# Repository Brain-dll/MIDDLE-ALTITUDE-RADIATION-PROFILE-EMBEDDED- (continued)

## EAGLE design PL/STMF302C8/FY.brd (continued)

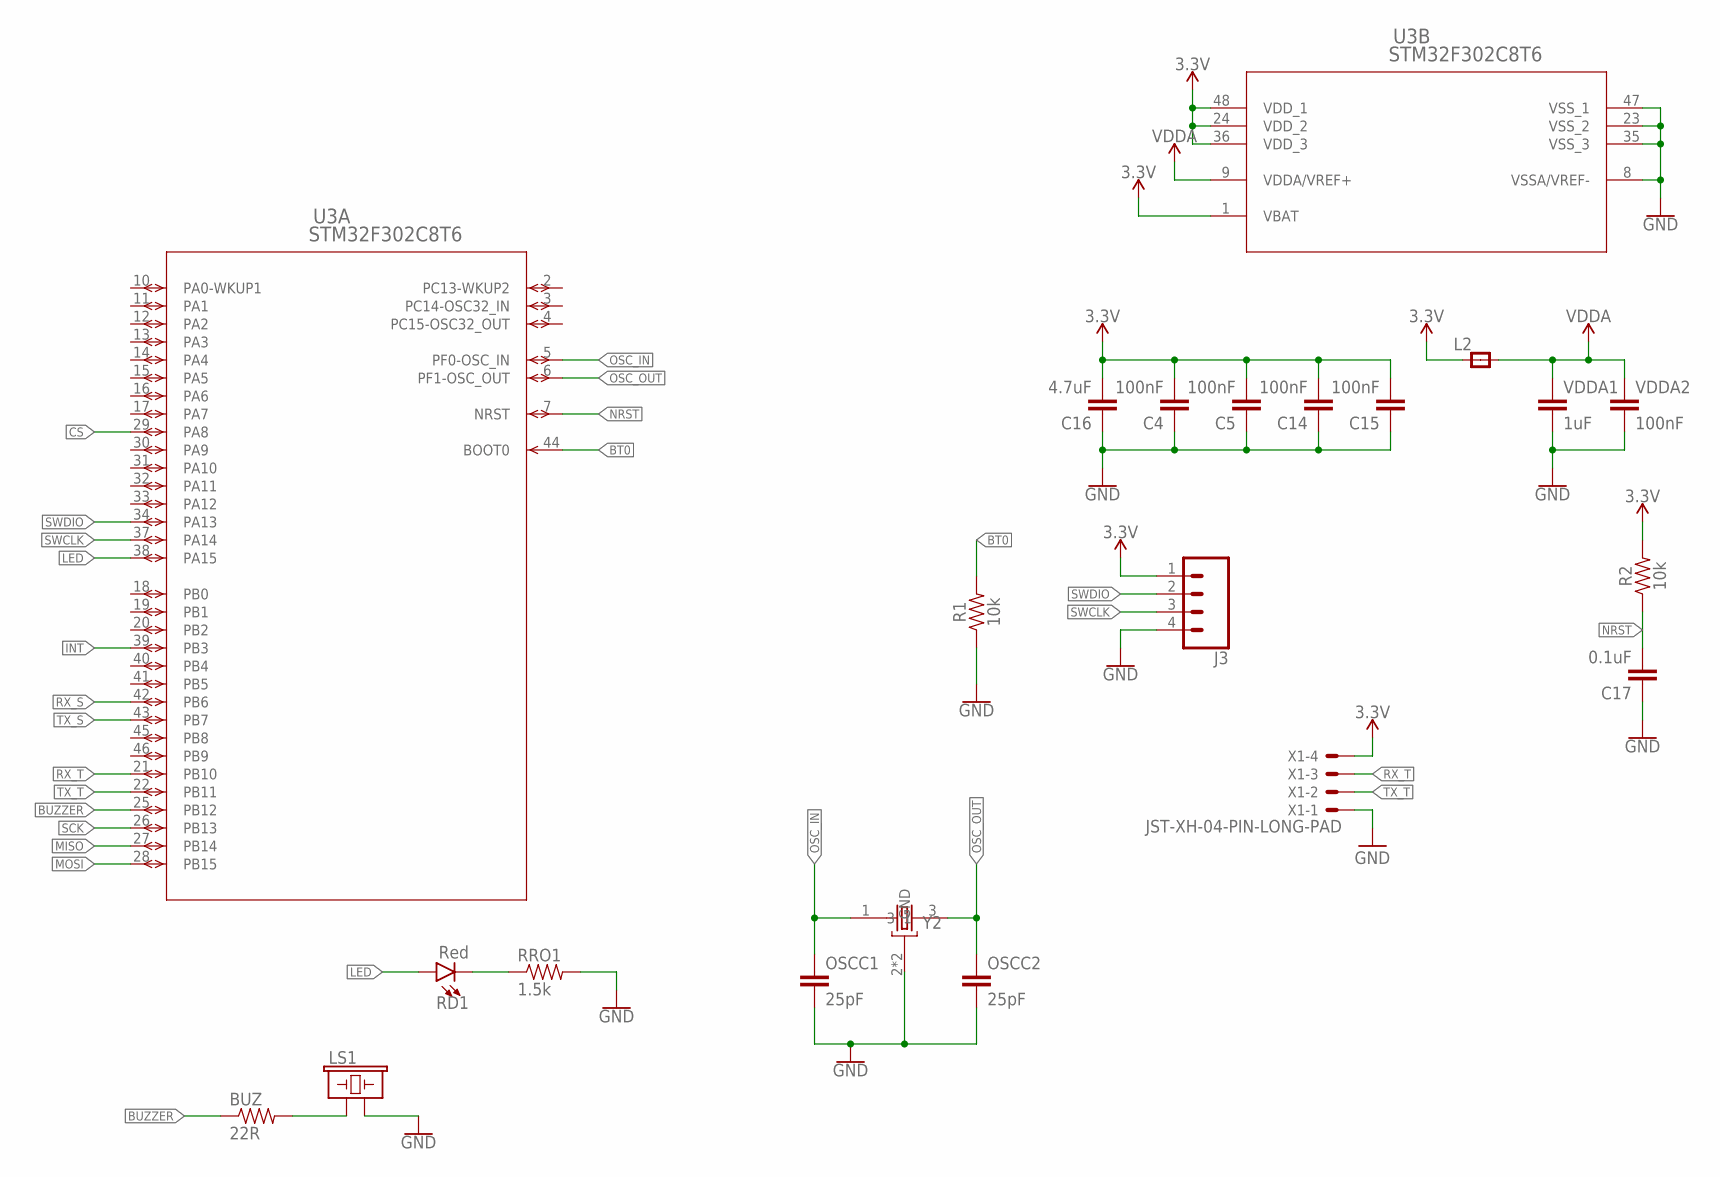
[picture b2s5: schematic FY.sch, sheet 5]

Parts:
BUZ: 22R; 0603-RES
C4, C5, C14, C15: 100nF; 0603
C16: 4.7uF; 0603
C17: 0.1uF; 0603
J3: CONN_04; 1X04
L2: RC-MASTER-SMD_FB_0805MP; RC-MASTER-SMD_L0805MP
LS1: BUZZER-PTH; BUZZER-12MM
OSCC1, OSCC2: 25pF; 0603
R1, R2: 10k; 0603
RD1: Red; LED-0603
RRO1: 1.5k; 0603-RES
U3: STM32F302C8T6; LQFP48-7X7MM
VDDA1: 1uF; 0603
VDDA2: 100nF; 0603
X1: JST-XH-04-PIN-LONG-PAD; JST-XH-04-PACKAGE-LONG-PAD
Y2: ABM2B-8.000MHZ-10-1-U-T; OSCCC500X320X110-4N

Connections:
3.3V: C4.2, C5.2, C14.2, C15.2, C16.2, J3.1, L2.1, R2.2, U3.1 (VBAT), U3.24 (VDD_2), U3.36 (VDD_3), U3.48 (VDD_1), X1.4; also elsewhere on the board
BT0: R1.2, U3.44 (BOOT0)
BUZZER: BUZ.1, U3.25 (PB12)
CS: U3.29 (PA8); also elsewhere on the board
GND: C4.1, C5.1, C14.1, C15.1, C16.1, C17.1, J3.4, LS1.- (2), OSCC1.2, OSCC2.2, R1.1, RRO1.2, U3.8 (VSSA/VREF-), U3.23 (VSS_2), U3.35 (VSS_3), U3.47 (VSS_1), VDDA1.2, VDDA2.2, X1.1, Y2.2 (GND), Y2.4 (GND); also elsewhere on the board
INT: U3.39 (PB3); also elsewhere on the board
LED: RD1.A, U3.38 (PA15)
MISO: U3.27 (PB14); also elsewhere on the board
MOSI: U3.28 (PB15); also elsewhere on the board
unnamed: RD1.C, RRO1.1
unnamed: BUZ.2, LS1.+ (1)
NRST: C17.2, R2.1, U3.7 (NRST)
OSC_IN: OSCC1.1, U3.5 (PF0-OSC_IN), Y2.1
OSC_OUT: OSCC2.1, U3.6 (PF1-OSC_OUT), Y2.3
RX_S: U3.42 (PB6); also elsewhere on the board
RX_T: U3.21 (PB10), X1.3
SCK: U3.26 (PB13); also elsewhere on the board
SWCLK: J3.3, U3.37 (PA14)
SWDIO: J3.2, U3.34 (PA13)
TX_S: U3.43 (PB7); also elsewhere on the board
TX_T: U3.22 (PB11), X1.2
VDDA: L2.2, U3.9 (VDDA/VREF+), VDDA1.1, VDDA2.1

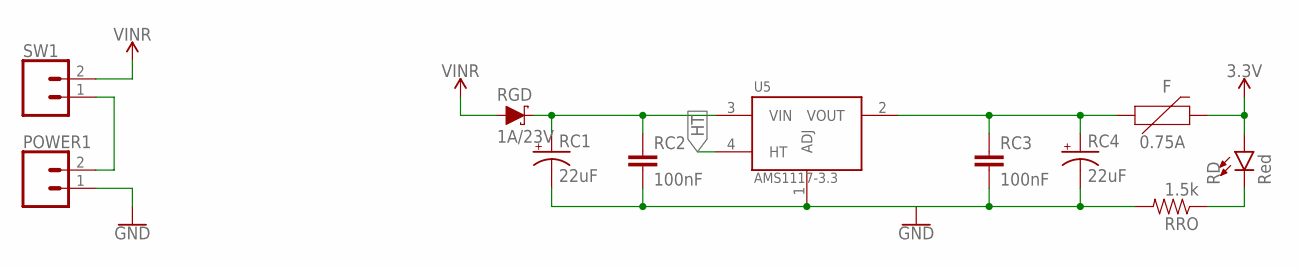
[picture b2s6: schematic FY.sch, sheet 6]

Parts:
F: 0.75A; 1206
POWER1: CONN_023.5MM-NO_SILK; SCREWTERMINAL-3.5MM-2-NS
RC1, RC4: 22uF; EIA3528
RC2, RC3: 100nF; 0603
RD: Red; LED-0603
RGD: 1A/23V; SOD-323
RRO: 1.5k; 0603-RES
SW1: CONN_023.5MM-NO_SILK; SCREWTERMINAL-3.5MM-2-NS
U5: AMS1117-3.3; SOT229P700X180-4N

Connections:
3.3V: F.2, RD.A; also elsewhere on the board
GND: POWER1.1, RC1.C (-), RC2.2, RC3.2, RC4.C (-), RRO.2, U5.1 (ADJ); also elsewhere on the board
HT: U5.4 (HT)
unnamed: POWER1.2, SW1.1
unnamed: F.1, RC3.1, RC4.A (+), U5.2 (VOUT)
unnamed: RD.C, RRO.1
VIN: RGD.A, SW1.2
VNR: RC1.A (+), RC2.1, RGD.C, U5.3 (VIN)

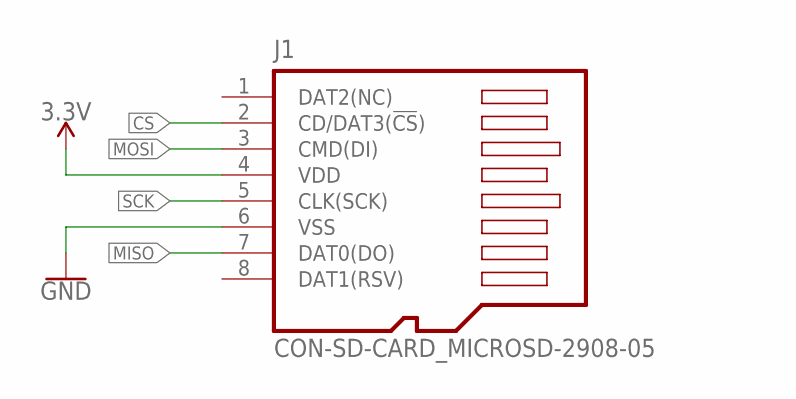
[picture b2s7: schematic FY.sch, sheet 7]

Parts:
J1: CON-SD-CARD_MICROSD-2908-05; CON-SD-CARD_2908-05

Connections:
3.3V: J1.4 (VDD); also elsewhere on the board
CS: J1.2 (CD/DAT3(!CS!)); also elsewhere on the board
GND: J1.6 (VSS); also elsewhere on the board
MISO: J1.7 (DAT0(DO)); also elsewhere on the board
MOSI: J1.3 (CMD(DI)); also elsewhere on the board
SCK: J1.5 (CLK(SCK)); also elsewhere on the board

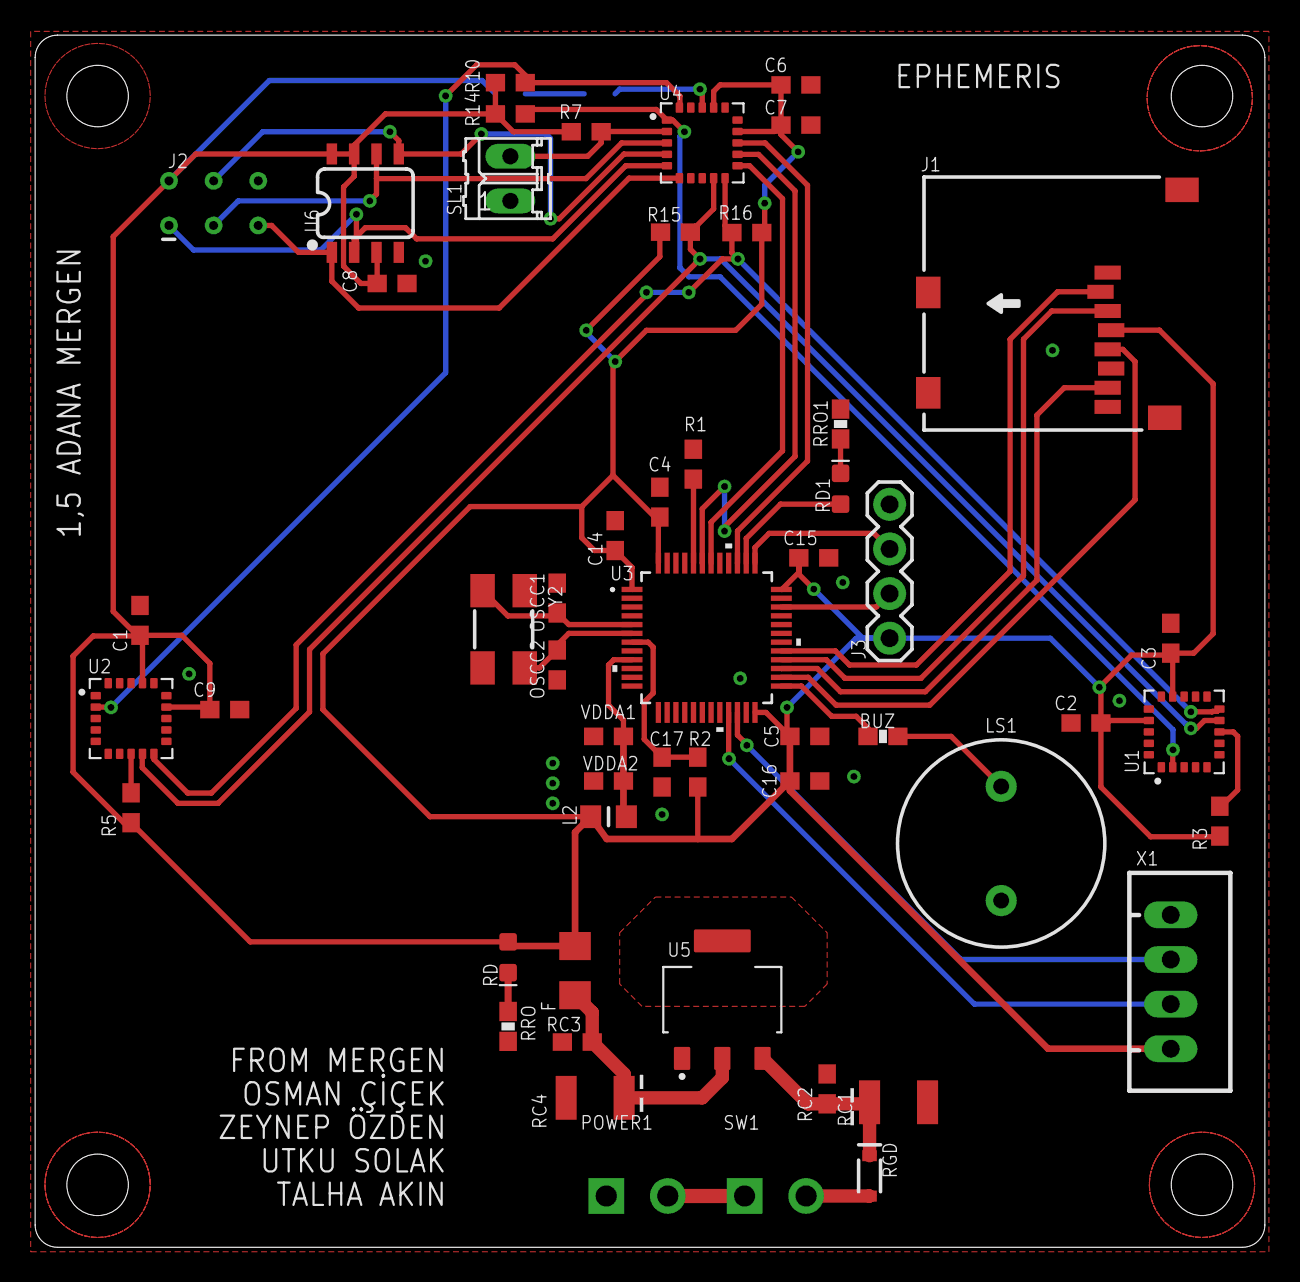
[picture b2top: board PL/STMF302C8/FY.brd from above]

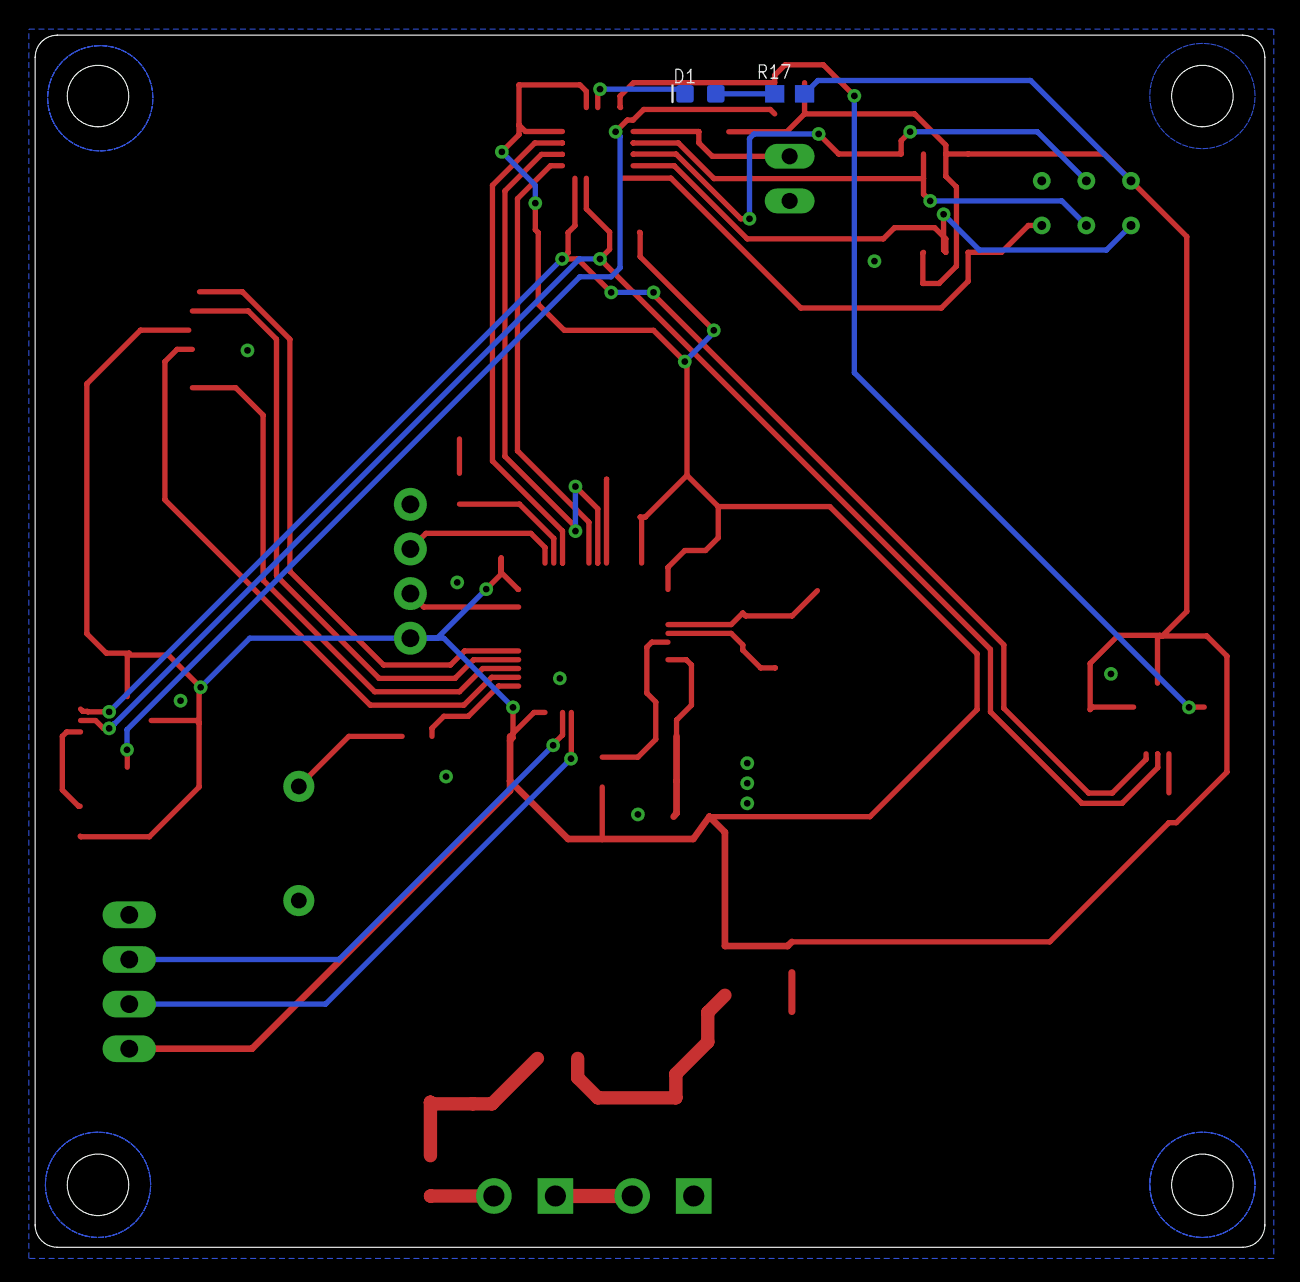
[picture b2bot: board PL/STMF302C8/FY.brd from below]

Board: 2 copper layers, 70.0 x 69.0 mm, 55 parts (2 on the bottom side), 40 nets.

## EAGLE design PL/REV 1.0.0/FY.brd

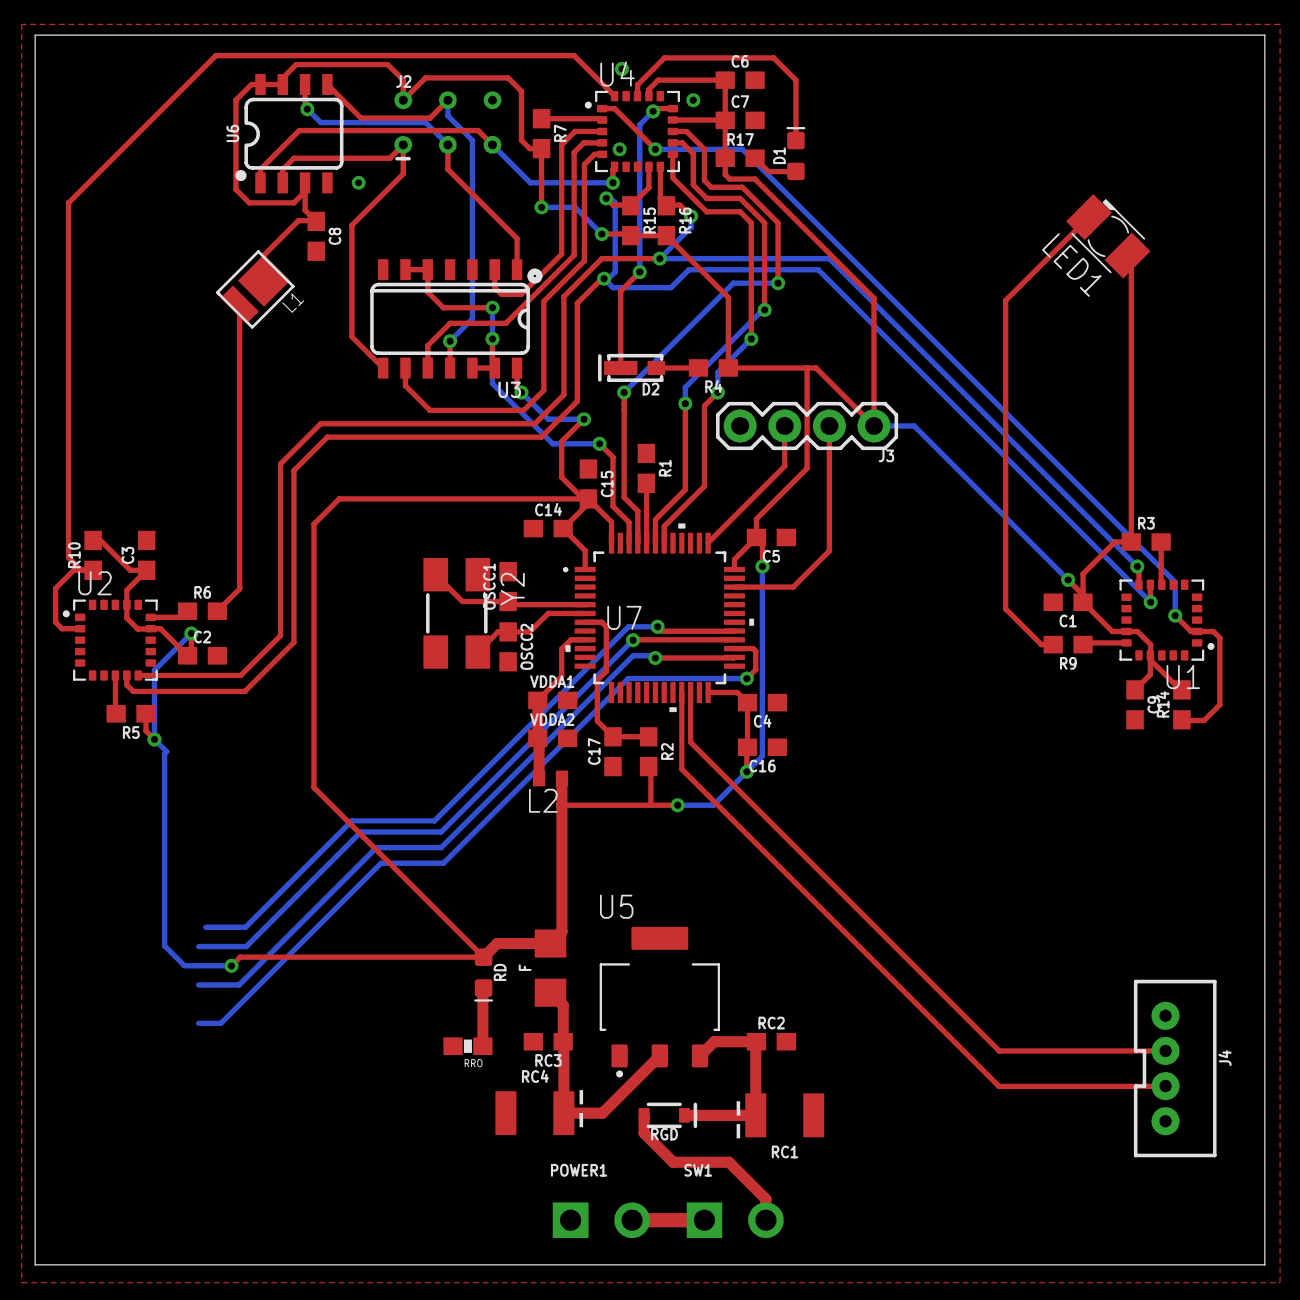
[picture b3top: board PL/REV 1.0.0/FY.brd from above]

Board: 2 copper layers, 70.0 x 70.0 mm, 57 parts (1 on the bottom side), 46 nets.

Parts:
C1, C2, C6: 1uF; 0603
C3, C4, C5, C7, C9, C14, C15: 100nF; 0603
C8: 1.0uF; 0603
C16: 4.7uF; 0603
C17: 0.1uF; 0603
D1: GREEN; LED-0603
D2: 5700k; SUPER_BRIGHT_SMD_LED_3014
F: 0.75A; 1206
J1: CON-SD-CARD_MICROSD-2908-05; CON-SD-CARD_2908-05
J2: Flash Programming; 2X3_TEST_POINTS
J3: 1X04
J4: JST-4-PTH-VERT
L1: 150283DS73103
L2: BLM15HB221SN1; 0402
LED1: KA-3528ASYC
OSCC1, OSCC2: 25pF; 0603
POWER1: SCREWTERMINAL-3.5MM-2-NS
R1, R2, R3, R5, R7, R10, R14, R15, R16: 10k; 0603
R4, R6, R9: 200; 0603
R17: 330; 0603
RC1, RC4: 22uF; EIA3528
RC2, RC3: 100nF; 0603
RD: Red; LED-0603
RGD: 1A/23V; SOD-323
RRO: 1.5k; 0603-RES
SW1: SCREWTERMINAL-3.5MM-2-NS
U1: AS72652-BLGT; PQFN65P470X450X270-20N
U2: AS72653-BLGT; PQFN65P470X450X270-20N
U3: 74LVC4066; SO14
U4: AS72651-BLGT; PQFN65P470X450X270-20N
U5: AMS1117-3.3; SOT229P700X180-4N
U6: 4MB Flash; SO08
U7: LQFP48-7X7MM
VDDA1: 1uF; 0603
VDDA2: 100nF; 0603
Y2: ABM2B-8.000MHZ-10-1-U-T; OSCCC500X320X110-4N

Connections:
3.3V: C1.1, C2.1, C3.1, C4.2, C5.2, C6.1, C7.1, C8.1, C9.1, C14.2, C15.2, C16.2, F.2, J1.4, J2.2, J3.1, L1.1, L2.1, LED1.A, R2.2, R3.1, R4.1, R5.1, R7.2, R10.2, R14.2, R15.2, R16.2, R17.1, RD.A, U1.14, U1.17, U2.14, U2.17, U3.14, U4.14, U4.17, U6.3, U6.7, U6.8, U7.1, U7.24, U7.36, U7.48
BT0: R1.2, U7.44
CMISO: U3.9, U4.5
CMOSI: U3.10, U4.4
CS: J1.2, U7.29
CSCK: U3.2, U4.3
CSN_EE: J2.5, U4.6, U6.1
CTRLA: U3.5, U3.6, U3.12, U3.13, U7.46
FMISO: J2.1, U3.8, U6.2
FMOSI: J2.4, U3.11, U6.5
FSCK: J2.3, U3.1, U6.6
GND: C1.2, C2.2, C3.2, C4.1, C5.1, C6.2, C7.2, C8.2, C9.2, C14.1, C15.1, C16.1, C17.1, J1.6, J2.6, J3.4, J4.1, J4.4, OSCC1.2, OSCC2.2, POWER1.1, R1.1, RC1.C, RC2.2, RC3.2, RC4.C, RRO.2, U1.16, U2.16, U3.7, U4.8, U4.16, U5.1, U6.4, U7.8, U7.23, U7.35, U7.47, VDDA1.2, VDDA2.2, Y2.2, Y2.4
INT: U4.13, U7.45
LED_DRV: D2.C, U4.15
LED_IND: D1.C, U4.18
MISO: J1.7, U7.27
MOSI: J1.3, U7.28
unnamed: R3.2, U1.8
unnamed: R6.1, U2.15
unnamed: POWER1.2, SW1.1
unnamed: L1.2, R6.2
unnamed: R5.2, U2.8
unnamed: F.1, RC3.1, RC4.A, U5.2
unnamed: R9.1, U1.15
unnamed: LED1.C, R9.2
unnamed: R7.1, U4.2
unnamed: RD.C, RRO.1
unnamed: D2.A, R4.2
unnamed: D1.A, R17.2
NRST: C17.2, R2.1, U7.7
OSC_IN: OSCC1.1, U7.5, Y2.1
OSC_OUT: OSCC2.1, U7.6, Y2.3
RX_S: U4.11, U7.42
RX_T: J4.3, U7.21
SCK: J1.5, U7.26
SCL_M: R15.1, U1.9, U2.9, U4.9
SDA_M: R16.1, U1.10, U2.10, U4.10
SLV1_R: R14.1, U1.2, U4.1
SLV2_R: R10.1, U2.2, U4.20
SWCLK: J3.3, U7.37
SWDIO: J3.2, U7.34
TX_S: U4.12, U7.43
TX_T: J4.2, U7.22
VDDA: L2.2, U7.9, VDDA1.1, VDDA2.1
VIN: RGD.A, SW1.2
VNR: RC1.A, RC2.1, RGD.C, U5.3

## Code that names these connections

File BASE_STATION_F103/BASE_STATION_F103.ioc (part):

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Mcu.Name=STM32F103C(8-B)Tx
Mcu.Package=LQFP48
Mcu.UserName=STM32F103C8Tx
PA0-WKUP.GPIOParameters=GPIO_Label
PA0-WKUP.GPIO_Label=M0
PA0-WKUP.Signal=GPIO_Output
PA1.GPIOParameters=GPIO_Label
PA1.GPIO_Label=M1
PA1.Signal=GPIO_Output
PA10.Mode=Asynchronous
PA10.Signal=USART1_RX
PA13.Mode=Serial_Wire
PA13.Signal=SYS_JTMS-SWDIO
PA14.Mode=Serial_Wire
PA14.Signal=SYS_JTCK-SWCLK
PA2.Mode=Asynchronous
PA2.Signal=USART2_TX
PA3.Mode=Asynchronous
PA3.Signal=USART2_RX
PA7.GPIOParameters=GPIO_Label
PA7.GPIO_Label=LED2
PA7.Signal=GPIO_Output
PA9.Mode=Asynchronous
PA9.Signal=USART1_TX
PB0.GPIOParameters=GPIO_Label
PB0.GPIO_Label=LED
PB0.Signal=GPIO_Output
PB10.Mode=Asynchronous
PB10.Signal=USART3_TX
PB11.Mode=Asynchronous
PB11.Signal=USART3_RX
PB12.GPIOParameters=GPIO_Label
PB12.GPIO_Label=SDCARD_CS
PB12.Signal=GPIO_Output
PB13.Mode=Full_Duplex_Master
PB13.Signal=SPI2_SCK
PB14.Mode=Full_Duplex_Master
PB14.Signal=SPI2_MISO
PB15.Mode=Full_Duplex_Master
PB15.Signal=SPI2_MOSI
PB4.GPIOParameters=GPIO_Label
PB4.GPIO_Label=BUZZER
PB4.Signal=GPIO_Output
PB6.Mode=I2C
PB6.Signal=I2C1_SCL
PB7.Mode=I2C
PB7.Signal=I2C1_SDA
PD0-OSC_IN.Mode=HSE-External-Oscillator
PD0-OSC_IN.Signal=RCC_OSC_IN
PD1-OSC_OUT.Mode=HSE-External-Oscillator
PD1-OSC_OUT.Signal=RCC_OSC_OUT
RCC.SYSCLKFreq_VALUE=72000000
RCC.SYSCLKSource=RCC_SYSCLKSOURCE_PLLCLK
board=custom

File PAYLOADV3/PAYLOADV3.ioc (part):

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Mcu.Name=STM32F103C(8-B)Tx
Mcu.Package=LQFP48
Mcu.UserName=STM32F103C8Tx
PA13.Mode=Serial_Wire
PA13.Signal=SYS_JTMS-SWDIO
PA14.Mode=Serial_Wire
PA14.Signal=SYS_JTCK-SWCLK
PA2.Mode=Asynchronous
PA2.Signal=USART2_TX
PA3.Mode=Asynchronous
PA3.Signal=USART2_RX
PA7.GPIOParameters=GPIO_Label
PA7.GPIO_Label=LED
PA7.Signal=GPIO_Output
PA8.GPIOParameters=GPIO_Label
PA8.GPIO_Label=SD_CS
PA8.Signal=GPIO_Output
PB0.GPIOParameters=GPIO_Label
PB0.GPIO_Label=BUZZER
PB0.Signal=GPIO_Output
PB13.Mode=Full_Duplex_Master
PB13.Signal=SPI2_SCK
PB14.Mode=Full_Duplex_Master
PB14.Signal=SPI2_MISO
PB15.Mode=Full_Duplex_Master
PB15.Signal=SPI2_MOSI
PB6.Mode=Asynchronous
PB6.Signal=USART1_TX
PB7.Mode=Asynchronous
PB7.Signal=USART1_RX
PB8.Mode=I2C
PB8.Signal=I2C1_SCL
PB9.Mode=I2C
PB9.Signal=I2C1_SDA
PD0-OSC_IN.Mode=HSE-External-Oscillator
PD0-OSC_IN.Signal=RCC_OSC_IN
PD1-OSC_OUT.Mode=HSE-External-Oscillator
PD1-OSC_OUT.Signal=RCC_OSC_OUT
RCC.SYSCLKFreq_VALUE=72000000
RCC.SYSCLKSource=RCC_SYSCLKSOURCE_PLLCLK
board=custom

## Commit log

2021-03-26 New version of boards with new controller was designed
2021-03-28 Connector was changed and Preparing first order
2021-04-03 Polygon witdh was increased IMPOTANT**
2021-04-03 Polygon 15 mils
2021-04-08 packages was modified according to stock situation
2021-04-19 Some modification was done
2021-05-03 Component name locations was arranged
2021-06-15 Version 2.0 was relased by brain.dll
2021-06-15 distance holl was putted
2021-06-15 Magnetometer was added by brain.dll
2021-06-30 holes were moved and VDDA cap value was changed
2021-07-05 05.07.2021
2021-08-08 Software and Algorithm was added
2021-08-11 Sofware was added
2021-08-15 Sofware was updated
2021-09-01 Last updates was completed, Ready for flying
2021-09-17 Sofware and and hardware are stable
2021-09-17 Unneccessary file was deleted
